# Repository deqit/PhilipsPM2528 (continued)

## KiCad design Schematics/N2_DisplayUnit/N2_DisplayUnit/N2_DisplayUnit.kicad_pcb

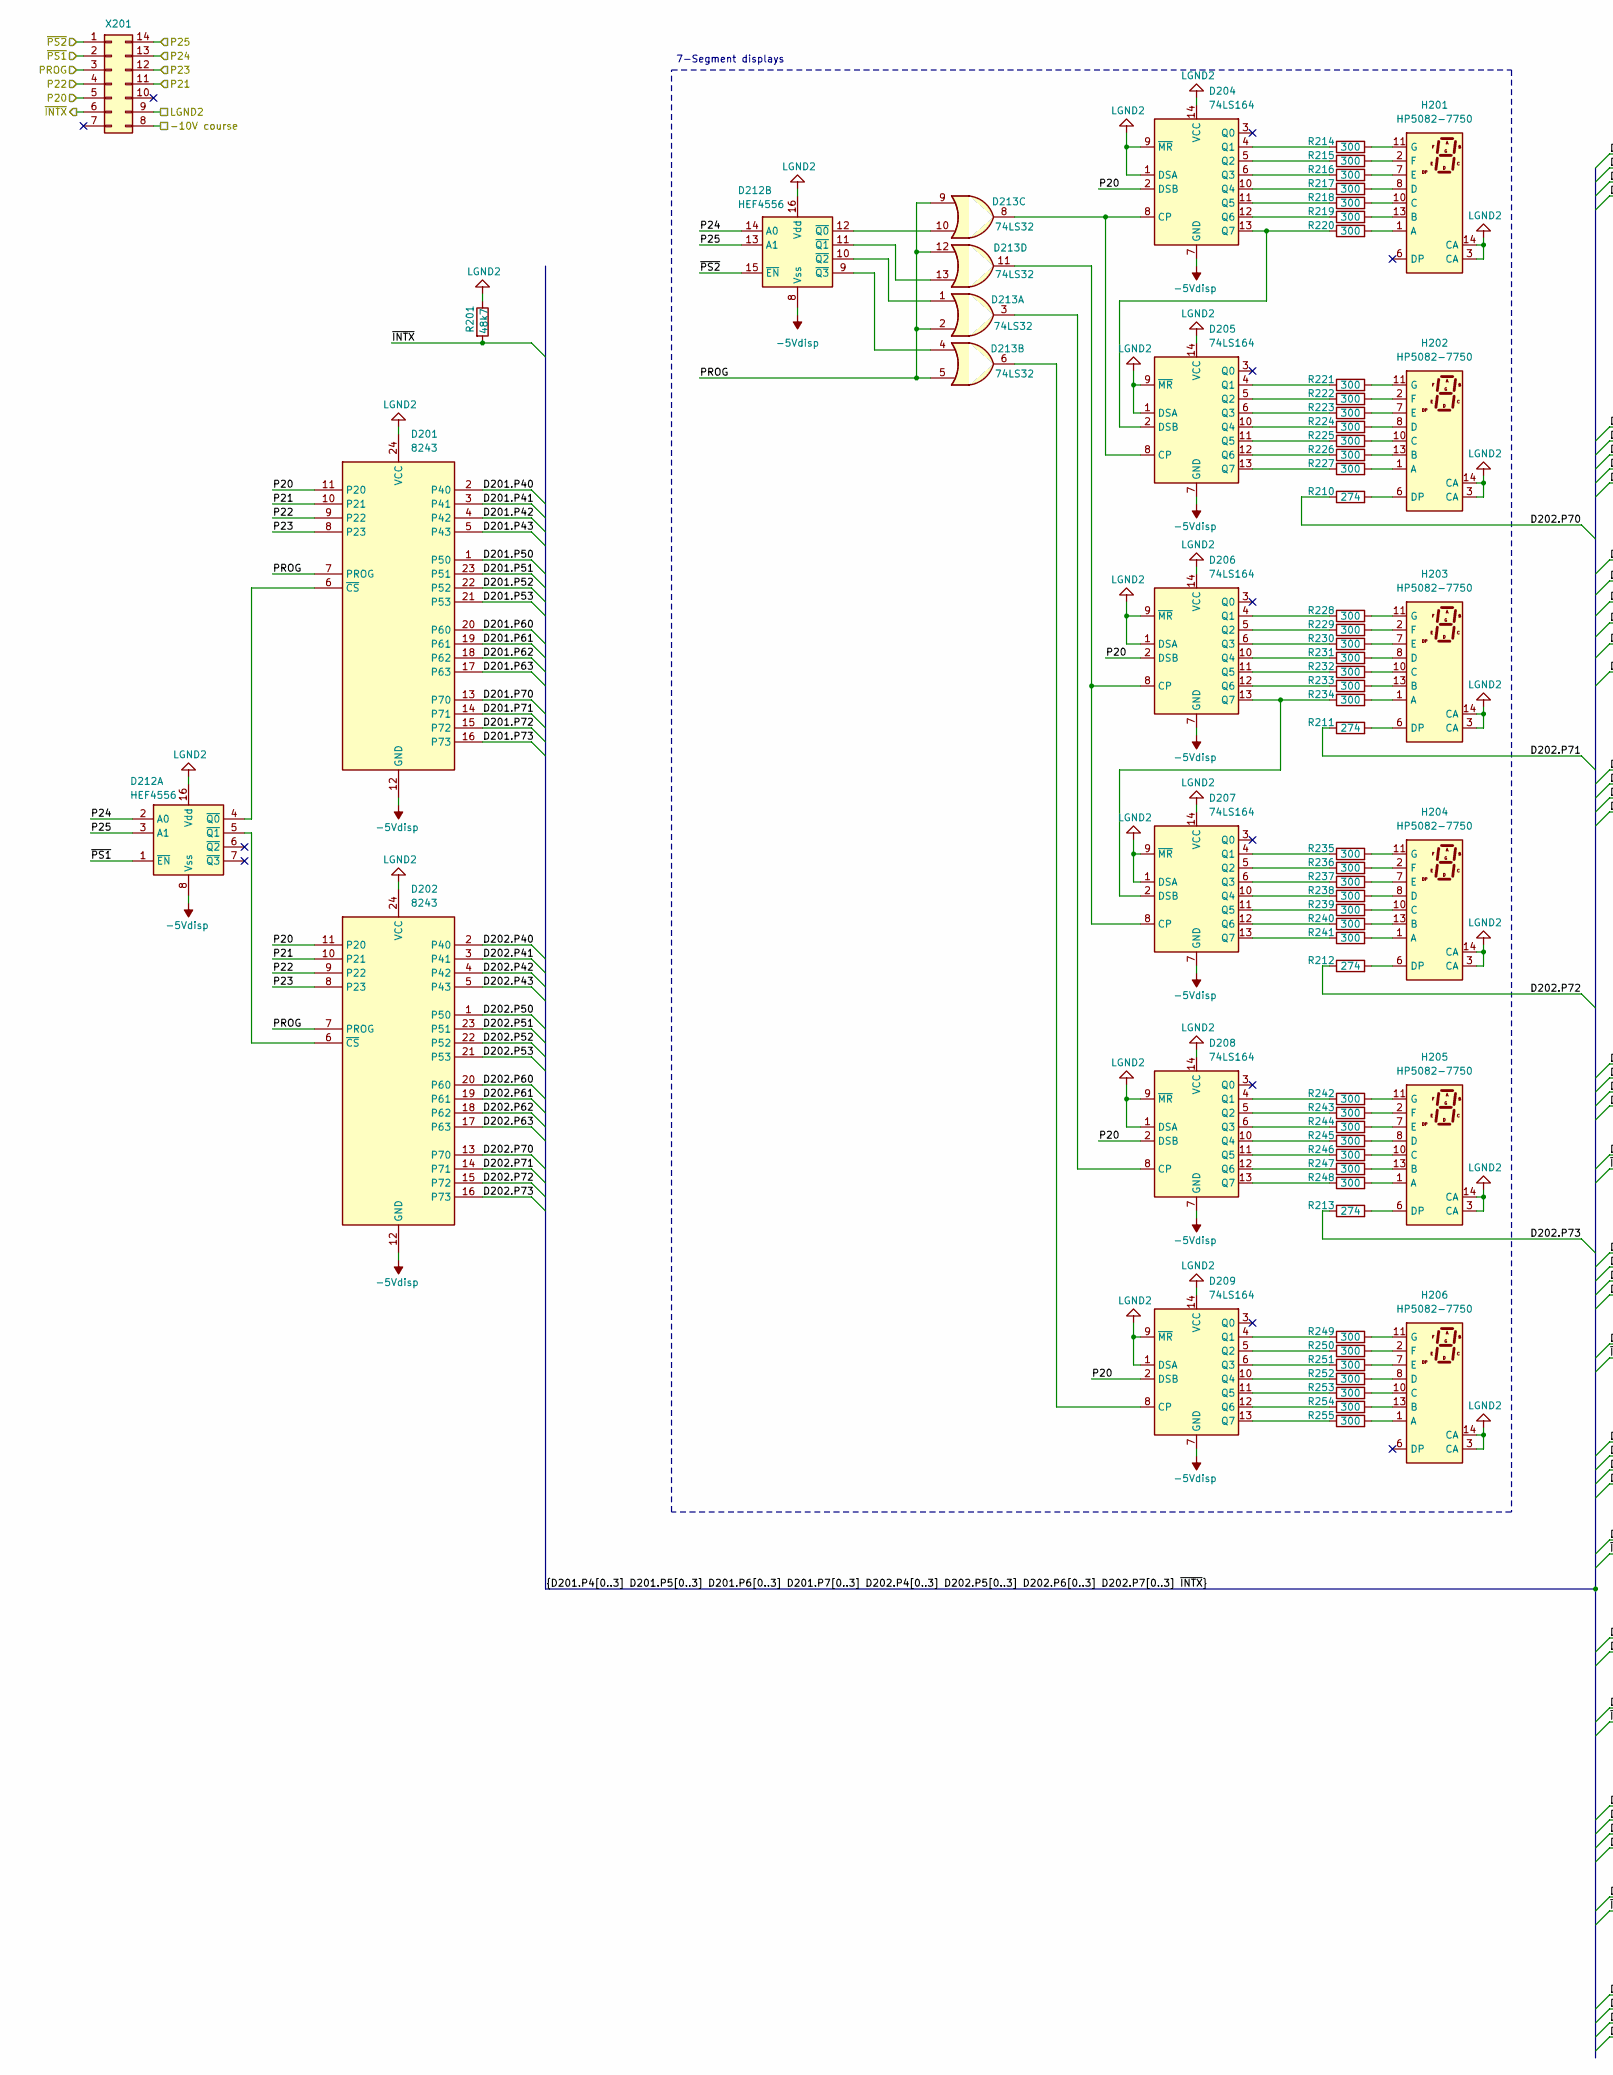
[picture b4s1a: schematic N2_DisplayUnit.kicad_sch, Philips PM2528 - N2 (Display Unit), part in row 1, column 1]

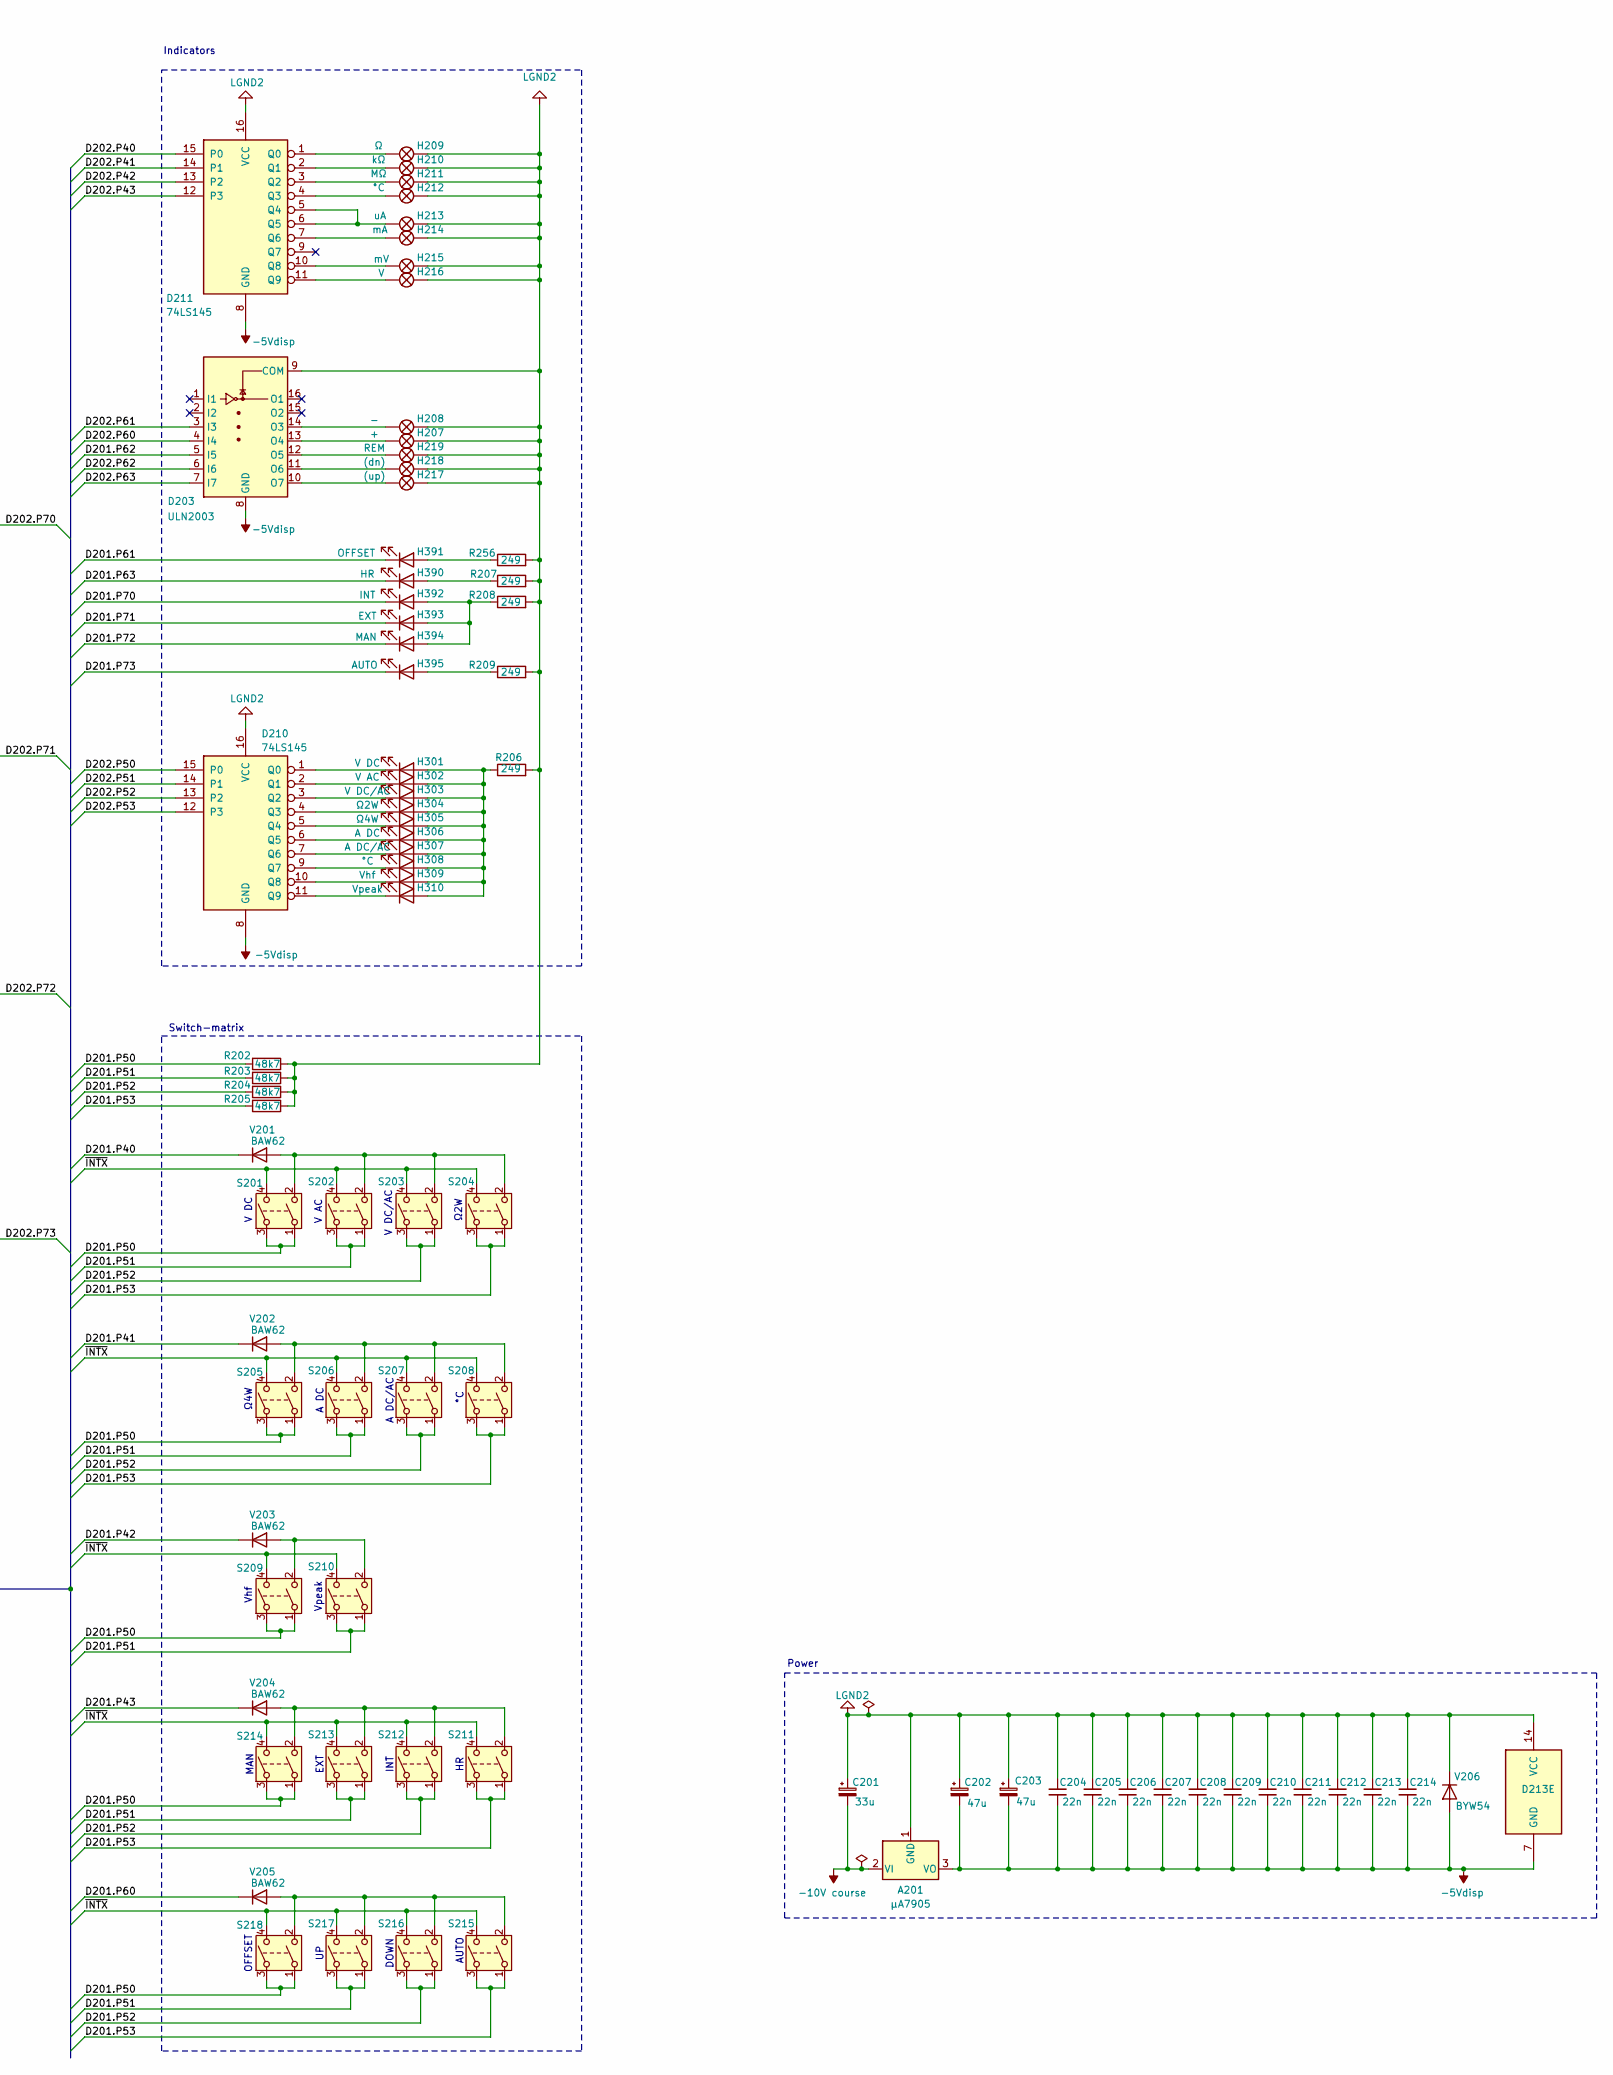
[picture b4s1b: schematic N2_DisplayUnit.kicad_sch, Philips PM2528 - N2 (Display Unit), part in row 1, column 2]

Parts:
A201: µA7905; TO-220-3_Vertical
C201: 33u; CP_Axial_L10.0mm_D4.5mm_P15.00mm_Horizontal
C202, C203: 47u; CP_Axial_L10.0mm_D4.5mm_P15.00mm_Horizontal
C204, C205, C206, C207, C208, C209, C210, C211, C212, C213, C214: 22n; C_Disc_D5.0mm_W2.5mm_P5.00mm
D201, D202: 8243; DIP-24_W15.24mm
D203: ULN2003; DIP-16_W7.62mm
D204, D205, D206, D207, D208, D209: 74LS164; DIP-14_W7.62mm
D210, D211: 74LS145; DIP-16_W7.62mm
D212: HEF4556; DIP-16_W7.62mm
D213: 74LS32; DIP-14_W7.62mm
H201, H202, H203, H204, H205, H206: HP5082-7750; MAN3820A
H207: +; LED_D3.0mm
H208: -; LED_D3.0mm
H209: Ω; LED_D3.0mm
H210: kΩ; LED_D3.0mm
H211: MΩ; LED_D3.0mm
H212, H308: °C; LED_D3.0mm
H213: uA; LED_D3.0mm
H214: mA; LED_D3.0mm
H215: mV; LED_D3.0mm
H216: V; LED_D3.0mm
H217: (up); LED_D3.0mm
H218: (dn); LED_D3.0mm
H219: REM; LED_D3.0mm
H301: V DC; LED_D3.0mm
H302: V AC; LED_D3.0mm
H303: V DC/AC; LED_D3.0mm
H304: Ω2W; LED_D3.0mm
H305: Ω4W; LED_D3.0mm
H306: A DC; LED_D3.0mm
H307: A DC/AC; LED_D3.0mm
H309: Vhf; LED_D3.0mm
H310: Vpeak; LED_D3.0mm
H390: HR; LED_D3.0mm
H391: OFFSET; LED_D3.0mm
H392: INT; LED_D3.0mm
H393: EXT; LED_D3.0mm
H394: MAN; LED_D3.0mm
H395: AUTO; LED_D3.0mm
R201, R202, R203, R204, R205: 48k7; R_Axial_DIN0207_L6.3mm_D2.5mm_P10.16mm_Horizontal
R206, R207, R208, R209, R256: 249; R_Axial_DIN0207_L6.3mm_D2.5mm_P10.16mm_Horizontal
R210, R211, R212, R213: 274; R_Axial_DIN0207_L6.3mm_D2.5mm_P10.16mm_Horizontal
R214, R215, R216, R217, R218, R219, R220, R221, R222, R223, R224, R225, R226, R227, R228, R229, R230, R231, R232, R233, R234, R235, R236, R237, R238, R239, R240, R241, R242, R243, R244, R245, R246, R247, R248, R249, R250, R251, R252, R253, R254, R255: 300; R_Axial_DIN0207_L6.3mm_D2.5mm_P2.54mm_Vertical
S201, S202, S203, S204, S205, S206, S207, S208, S209, S210, S211, S212, S213, S214, S215, S216, S217, S218: SW_DPST; SW_Push_2P1T_Toggle_CK_PVA1xxH1xxxxxxV2
V201, V202, V203, V204, V205: BAW62; D_DO-35_SOD27_P10.16mm_Horizontal
V206: BYW54; D_DO-35_SOD27_P10.16mm_Horizontal
X201: Conn_02x07_Counter_Clockwise; DIP-14_W10.16mm

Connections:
-5Vdisp: A201.3 (VO), C202.2, C203.2, C204.2, C205.2, C206.2, C207.2, C208.2, C209.2, C210.2, C211.2, C212.2, C213.2, C214.2, D201.12 (GND), D202.12 (GND), D203.8 (GND), D204.7 (GND), D205.7 (GND), D206.7 (GND), D207.7 (GND), D208.7 (GND), D209.7 (GND), D210.8 (GND), D211.8 (GND), D212.8 (Vss), D213.7 (GND), V206.2 (A)
-10V course: A201.2 (VI), C201.2, X201.8
/D201.P40: D201.2 (P40), V201.1 (K)
/D201.P41: D201.3 (P41), V202.1 (K)
/D201.P42: D201.4 (P42), V203.1 (K)
/D201.P43: D201.5 (P43), V204.1 (K)
/D201.P50: D201.1 (P50), R202.2, S201.1, S201.3, S205.1, S205.3, S209.1, S209.3, S214.1, S214.3, S218.1, S218.3
/D201.P51: D201.23 (P51), R203.2, S202.1, S202.3, S206.1, S206.3, S210.1, S210.3, S213.1, S213.3, S217.1, S217.3
/D201.P52: D201.22 (P52), R204.2, S203.1, S203.3, S207.1, S207.3, S212.1, S212.3, S216.1, S216.3
/D201.P53: D201.21 (P53), R205.2, S204.1, S204.3, S208.1, S208.3, S211.1, S211.3, S215.1, S215.3
/D201.P60: D201.20 (P60), V205.1 (K)
/D201.P61: D201.19 (P61), H391.1 (K)
/D201.P62: D201.18 (P62), D203.5 (I5)
/D201.P63: D201.17 (P63), H390.1 (K)
/D201.P70: D201.13 (P70), H392.1 (K)
/D201.P71: D201.14 (P71), H393.1 (K)
/D201.P72: D201.15 (P72), H394.1 (K)
/D201.P73: D201.16 (P73), H395.1 (K)
/D202.P40: D202.2 (P40), D211.15 (P0)
/D202.P41: D202.3 (P41), D211.14 (P1)
/D202.P42: D202.4 (P42), D211.13 (P2)
/D202.P43: D202.5 (P43), D211.12 (P3)
/D202.P50: D202.1 (P50), D210.15 (P0)
/D202.P51: D202.23 (P51), D210.14 (P1)
/D202.P52: D202.22 (P52), D210.13 (P2)
/D202.P53: D202.21 (P53), D210.12 (P3)
/D202.P60: D202.20 (P60), D203.4 (I4)
/D202.P61: D202.19 (P61), D203.3 (I3)
/D202.P62: D202.18 (P62), D203.6 (I6)
/D202.P63: D202.17 (P63), D203.7 (I7)
/D202.P70: D202.13 (P70), R210.1
/D202.P71: D202.14 (P71), R211.1
/D202.P72: D202.15 (P72), R212.1
/D202.P73: D202.16 (P73), R213.1
/LGND2: A201.1 (GND), C201.1, C202.1, C203.1, C204.1, C205.1, C206.1, C207.1, C208.1, C209.1, C210.1, C211.1, C212.1, C213.1, C214.1, D201.24 (VCC), D202.24 (VCC), D203.9 (COM), D204.1 (DSA), D204.9 (~MR), D204.14 (VCC), D205.1 (DSA), D205.9 (~MR), D205.14 (VCC), D206.1 (DSA), D206.9 (~MR), D206.14 (VCC), D207.1 (DSA), D207.9 (~MR), D207.14 (VCC), D208.1 (DSA), D208.9 (~MR), D208.14 (VCC), D209.1 (DSA), D209.9 (~MR), D209.14 (VCC), D210.16 (VCC), D211.16 (VCC), D212.16 (Vdd), D213.14 (VCC), H201.3 (CA), H201.14 (CA), H202.3 (CA), H202.14 (CA), H203.3 (CA), H203.14 (CA), H204.3 (CA), H204.14 (CA), H205.3 (CA), H205.14 (CA), H206.3 (CA), H206.14 (CA), H207.2, H208.2, H209.2, H210.2, H211.2, H212.2, H213.2, H214.2, H215.2, H216.2, H217.2, H218.2, H219.2, R201.1, R202.1, R203.1, R204.1, R205.1, R206.2, R207.2, R208.2, R209.2, R256.2, V206.1 (K), X201.9
/P20: D201.11 (P20), D202.11 (P20), D204.2 (DSB), D206.2 (DSB), D208.2 (DSB), D209.2 (DSB), X201.5
/P21: D201.10 (P21), D202.10 (P21), X201.11
/P22: D201.9 (P22), D202.9 (P22), X201.4
/P23: D201.8 (P23), D202.8 (P23), X201.12
/P24: D212.2 (A0), D212.14 (A0), X201.13
/P25: D212.3 (A1), D212.13 (A1), X201.14
/PROG: D201.7 (PROG), D202.7 (PROG), D213.2, D213.5, D213.9, D213.12, X201.3
/~INTX: R201.2, S201.4, S202.4, S203.4, S204.4, S205.4, S206.4, S207.4, S208.4, S209.4, S210.4, S211.4, S212.4, S213.4, S214.4, S215.4, S216.4, S217.4, S218.4, X201.6
/~PS1: D212.1 (~EN), X201.2
/~PS2: D212.15 (~EN), X201.1
unnamed: D201.6 (~CS), D212.4 (~Q0)
unnamed: D202.6 (~CS), D212.5 (~Q1)
unnamed: D203.14 (O3), H208.1
unnamed: D203.13 (O4), H207.1
unnamed: D203.12 (O5), H219.1
unnamed: D203.11 (O6), H218.1
unnamed: D203.10 (O7), H217.1
unnamed: D204.8 (CP), D205.8 (CP), D213.8
unnamed: D204.4 (Q1), R214.1
unnamed: D204.5 (Q2), R215.1
unnamed: D204.6 (Q3), R216.1
unnamed: D204.10 (Q4), R217.1
unnamed: D204.11 (Q5), R218.1
unnamed: D204.12 (Q6), R219.1
unnamed: D204.13 (Q7), D205.2 (DSB), R220.1
unnamed: D205.4 (Q1), R221.1
unnamed: D205.5 (Q2), R222.1
unnamed: D205.6 (Q3), R223.1
unnamed: D205.10 (Q4), R224.1
unnamed: D205.11 (Q5), R225.1
unnamed: D205.12 (Q6), R226.1
unnamed: D205.13 (Q7), R227.1
unnamed: D206.8 (CP), D207.8 (CP), D213.11
unnamed: D206.4 (Q1), R228.1
unnamed: D206.5 (Q2), R229.1
unnamed: D206.6 (Q3), R230.1
unnamed: D206.10 (Q4), R231.1
unnamed: D206.11 (Q5), R232.1
unnamed: D206.12 (Q6), R233.1
unnamed: D206.13 (Q7), D207.2 (DSB), R234.1
unnamed: D207.4 (Q1), R235.1
unnamed: D207.5 (Q2), R236.1
unnamed: D207.6 (Q3), R237.1
unnamed: D207.10 (Q4), R238.1
unnamed: D207.11 (Q5), R239.1
unnamed: D207.12 (Q6), R240.1
unnamed: D207.13 (Q7), R241.1
unnamed: D208.8 (CP), D213.3
unnamed: D208.4 (Q1), R242.1
unnamed: D208.5 (Q2), R243.1
unnamed: D208.6 (Q3), R244.1
unnamed: D208.10 (Q4), R245.1
unnamed: D208.11 (Q5), R246.1
unnamed: D208.12 (Q6), R247.1
unnamed: D208.13 (Q7), R248.1
unnamed: D209.8 (CP), D213.6
unnamed: D209.4 (Q1), R249.1
unnamed: D209.5 (Q2), R250.1
unnamed: D209.6 (Q3), R251.1
unnamed: D209.10 (Q4), R252.1
unnamed: D209.11 (Q5), R253.1
unnamed: D209.12 (Q6), R254.1
unnamed: D209.13 (Q7), R255.1
unnamed: D210.1 (Q0), H301.1 (K)
unnamed: D210.2 (Q1), H302.1 (K)
unnamed: D210.3 (Q2), H303.1 (K)
unnamed: D210.4 (Q3), H304.1 (K)
unnamed: D210.5 (Q4), H305.1 (K)
unnamed: D210.6 (Q5), H306.1 (K)
unnamed: D210.7 (Q6), H307.1 (K)
unnamed: D210.9 (Q7), H308.1 (K)
unnamed: D210.10 (Q8), H309.1 (K)
unnamed: D210.11 (Q9), H310.1 (K)
unnamed: D211.1 (Q0), H209.1
unnamed: D211.2 (Q1), H210.1
unnamed: D211.3 (Q2), H211.1
unnamed: D211.4 (Q3), H212.1
unnamed: D211.5 (Q4), D211.6 (Q5), H213.1
unnamed: D211.7 (Q6), H214.1
unnamed: D211.10 (Q8), H215.1
unnamed: D211.11 (Q9), H216.1
unnamed: D212.12 (~Q0), D213.10
unnamed: D212.11 (~Q1), D213.13
unnamed: D212.10 (~Q2), D213.1
unnamed: D212.9 (~Q3), D213.4
unnamed: H201.1 (A), R220.2
unnamed: H201.13 (B), R219.2
unnamed: H201.10 (C), R218.2
unnamed: H201.8 (D), R217.2
unnamed: H201.7 (E), R216.2
unnamed: H201.2 (F), R215.2
unnamed: H201.11 (G), R214.2
unnamed: H202.1 (A), R227.2
unnamed: H202.13 (B), R226.2
unnamed: H202.10 (C), R225.2
unnamed: H202.8 (D), R224.2
unnamed: H202.6 (DP), R210.2
unnamed: H202.7 (E), R223.2
unnamed: H202.2 (F), R222.2
unnamed: H202.11 (G), R221.2
unnamed: H203.1 (A), R234.2
unnamed: H203.13 (B), R233.2
unnamed: H203.10 (C), R232.2
unnamed: H203.8 (D), R231.2
unnamed: H203.6 (DP), R211.2
unnamed: H203.7 (E), R230.2
unnamed: H203.2 (F), R229.2
unnamed: H203.11 (G), R228.2
unnamed: H204.1 (A), R241.2
unnamed: H204.13 (B), R240.2
unnamed: H204.10 (C), R239.2
unnamed: H204.8 (D), R238.2
unnamed: H204.6 (DP), R212.2
unnamed: H204.7 (E), R237.2
unnamed: H204.2 (F), R236.2
unnamed: H204.11 (G), R235.2
unnamed: H205.1 (A), R248.2
unnamed: H205.13 (B), R247.2
unnamed: H205.10 (C), R246.2
unnamed: H205.8 (D), R245.2
unnamed: H205.6 (DP), R213.2
unnamed: H205.7 (E), R244.2
unnamed: H205.2 (F), R243.2
unnamed: H205.11 (G), R242.2
unnamed: H206.1 (A), R255.2
unnamed: H206.13 (B), R254.2
unnamed: H206.10 (C), R253.2
unnamed: H206.8 (D), R252.2
unnamed: H206.7 (E), R251.2
unnamed: H206.2 (F), R250.2
unnamed: H206.11 (G), R249.2
unnamed: H301.2 (A), H302.2 (A), H303.2 (A), H304.2 (A), H305.2 (A), H306.2 (A), H307.2 (A), H308.2 (A), H309.2 (A), H310.2 (A), R206.1
unnamed: H390.2 (A), R207.1
unnamed: H391.2 (A), R256.1
unnamed: H392.2 (A), H393.2 (A), H394.2 (A), R208.1
unnamed: H395.2 (A), R209.1
unnamed: S201.2, S202.2, S203.2, S204.2, V201.2 (A)
unnamed: S205.2, S206.2, S207.2, S208.2, V202.2 (A)
unnamed: S209.2, S210.2, V203.2 (A)
unnamed: S211.2, S212.2, S213.2, S214.2, V204.2 (A)
unnamed: S215.2, S216.2, S217.2, S218.2, V205.2 (A)

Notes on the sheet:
Vhf
AUTO
Power
OFFSET
MAN
DOWN
V AC
Indicators
V DC
Switch-matrix
A DC
V DC/AC
Vpeak
EXT
7-Segment displays
Ω4W
Ω2W
A DC/AC
INT

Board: 2 copper layers, 144 parts (0 on the bottom side), 176 nets, no tracks yet.

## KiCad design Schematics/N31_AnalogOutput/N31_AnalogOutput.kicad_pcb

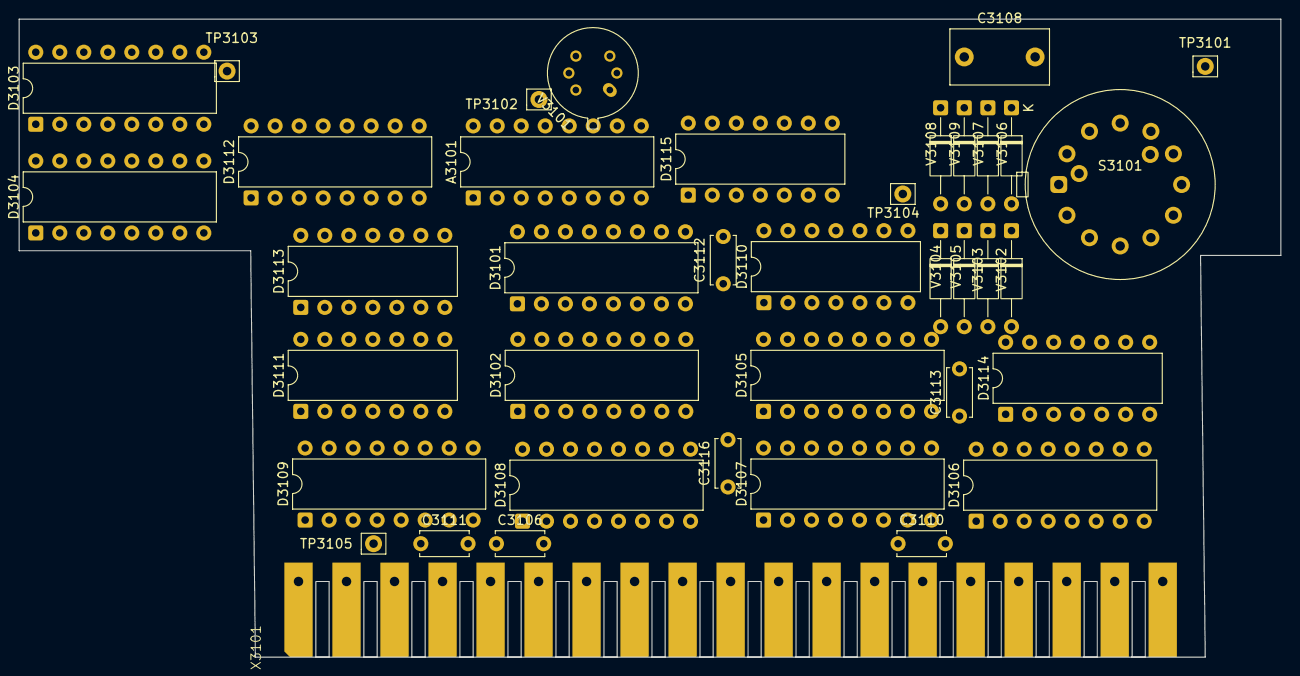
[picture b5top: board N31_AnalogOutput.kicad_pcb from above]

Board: 2 copper layers, 133.5 x 67.5 mm, 39 parts (0 on the bottom side), 71 nets, no tracks yet.

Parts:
A3101: OQ0051; DIP-16_W7.62mm
C3106, C3110, C3111, C3112, C3113, C3116: 22n; C_Disc_D5.0mm_W2.5mm_P5.00mm
C3108: 22n; C_Rect_L10.3mm_W5.7mm_P7.50mm_MKS4
D3101, D3102: HEF4094B; DIP-16_W7.62mm
D3103, D3104: HEF4040B; DIP-16_W7.62mm
D3105: HEF4008B; DIP-16_W7.62mm
D3106, D3107, D3108, D3109: HEF4522B; DIP-16_W7.62mm
D3110: HEF4085B; DIP-14_W7.62mm
D3111: HEF4011B; DIP-14_W7.62mm
D3112: HEF4049B; DIP-16_W7.62mm
D3113: HEF4073B; DIP-14_W7.62mm
D3114: HEF4081B; DIP-14_W7.62mm
D3115: HEF4066B; DIP-14_W7.62mm
S3101: DIGIT SELECT; RotarySwitch_1x7_S3101
TP3101: 0V; Pin_D0.9mm_L10.0mm_W2.4mm_FlatFork
TP3102: OUT; Pin_D0.9mm_L10.0mm_W2.4mm_FlatFork
TP3103: ≈850kHz; Pin_D0.9mm_L10.0mm_W2.4mm_FlatFork
TP3104: -7V; Pin_D0.9mm_L10.0mm_W2.4mm_FlatFork
TP3105: TerminalCount; Pin_D0.9mm_L10.0mm_W2.4mm_FlatFork
V3101: BFQ12; TO-75-6
V3102, V3103, V3104, V3105, V3106, V3107, V3108, V3109: BAW62; D_DO-35_SOD27_P10.16mm_Horizontal
X3101: PM2528Edgeconnector

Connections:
+5VOG: A3101.12 (V+), C3110.1, C3111.1, C3112.1, C3113.1, D3101.15 (EO), D3101.16 (VDD), D3102.15 (EO), D3102.16 (VDD), D3103.16 (VDD), D3104.16 (VDD), D3105.16 (VDD), D3106.13 (CF), D3106.16 (VDD), D3107.16 (VDD), D3108.16 (VDD), D3109.16 (VDD), D3110.14 (VDD), D3111.14 (VDD), D3112.1 (VDD), D3113.14 (VDD), D3114.14 (VDD), D3115.14 (VDD), S3101.8, X3101.5
-7V: A3101.1 (V-), C3116.2, TP3104.1 (1_1)
/CLOCK: D3113.13 (I9), X3101.19
/DATA: D3101.2 (D), X3101.18
/DLEN1: D3112.14 (6A), D3113.12 (I8), X3101.17
/HI: C3106.2, X3101.15
/LOAD: D3104.11 (MR), D3106.3 (PL), D3107.3 (PL), D3108.3 (PL), D3109.3 (PL), D3111.3 (O1)
/O0: D3102.4 (O0), D3108.2 (P3)
/O1: D3102.5 (O1), D3108.14 (P2)
/O2: D3102.6 (O2), D3108.11 (P1)
/O3: D3102.7 (O3), D3108.5 (P0)
/O4: D3102.14 (O4), D3109.2 (P3)
/O5: D3102.13 (O5), D3109.14 (P2)
/O6: D3102.12 (O6), D3109.11 (P1)
/O7: D3102.11 (O7), D3109.5 (P0)
/OP2: D3101.6 (O2), D3114.8 (I5)
/OP3: D3101.7 (O3), D3114.5 (I3)
/OP4: D3101.14 (O4), D3105.1 (A3), D3110.11 (B4)
/OP5: D3101.13 (O5), D3105.3 (A2), D3110.6 (B1), D3110.8 (B2)
/OP6: D3101.12 (O6), D3105.5 (A1), D3110.5 (B0)
/OP7: D3101.11 (O7), D3105.7 (A0), D3110.9 (B3)
/xDIGITSELECT_A: D3111.8 (I5), D3111.9 (I6), D3113.5 (I3), D3114.6 (I4), D3114.9 (I6), S3101.1
/xDIGITSELECT_C: D3105.6 (B0), D3114.1 (I1), D3114.13 (I8), S3101.3, V3103.1, V3105.1
/xDIGITSELECT_D: D3110.12 (A2), S3101.4, V3102.1
/xDIGITSELECT_F: D3110.2 (A1), S3101.6, V3104.1
/xOSC: D3104.10 (~CP), D3109.6 (CP0), D3112.4 (2Y), D3112.9 (4A), D3112.11 (5A), TP3103.1 (1_1)
/~Os: D3101.10 (O'_{S}), D3102.2 (D)
GNDOG: C3106.1, C3108.2, C3110.2, C3111.2, C3112.2, C3113.2, C3116.1, D3101.8 (VSS), D3102.8 (VSS), D3103.8 (VSS), D3104.8 (VSS), D3105.8 (VSS), D3105.9 (C_{IN}), D3106.2 (P3), D3106.4 (~CP1), D3106.8 (VSS), D3106.10 (MR), D3106.14 (P2), D3107.4 (~CP1), D3107.8 (VSS), D3107.10 (MR), D3108.4 (~CP1), D3108.8 (VSS), D3108.10 (MR), D3109.8 (VSS), D3109.10 (MR), D3110.7 (VSS), D3110.10 (A4), D3111.7 (VSS), D3112.8 (VSS), D3113.7 (VSS), D3114.7 (VSS), D3115.1 (Y0), D3115.3 (Z1), D3115.7 (VSS), D3115.9 (Z2), D3115.13 (E0), TP3101.1 (1_1), V3106.1, X3101.1, X3101.14
unnamed: A3101.15 (D_{IN+}), V3101.2 (D)
unnamed: A3101.14 (D_{IN-}), V3101.5 (D)
unnamed: A3101.4 (OUT2), A3101.5, TP3102.1 (1_1), V3101.6 (G)
unnamed: C3108.1, V3101.3 (G)
unnamed: D3101.3 (CP), D3102.3 (CP), D3103.10 (~CP), D3113.10 (O3)
unnamed: D3101.1 (STR), D3102.1 (STR), D3103.11 (MR), D3112.15 (6Y)
unnamed: D3103.6 (O2), D3113.2 (I5), D3113.8 (I6)
unnamed: D3103.3 (O4), D3110.1 (A0), D3113.1 (I4)
unnamed: D3104.14 (O9), D3113.4 (I2)
unnamed: D3104.15 (O10), D3111.6 (I4)
unnamed: D3104.1 (O11), D3113.3 (I1)
unnamed: D3105.4 (B1), D3105.15 (B3), D3114.11 (O4)
unnamed: D3105.2 (B2), D3114.3 (O1)
unnamed: D3105.10 (S0), D3107.5 (P0)
unnamed: D3105.11 (S1), D3107.11 (P1)
unnamed: D3105.12 (S2), D3107.14 (P2)
unnamed: D3105.13 (S3), D3107.2 (P3)
unnamed: D3106.6 (CP0), D3107.1 (O3)
unnamed: D3106.5 (P0), D3114.4 (O2)
unnamed: D3106.11 (P1), D3114.10 (O3)
unnamed: D3106.12 (TC), D3107.13 (CF)
unnamed: D3107.6 (CP0), D3108.1 (O3)
unnamed: D3107.12 (TC), D3108.13 (CF)
unnamed: D3108.6 (CP0), D3109.1 (O3)
unnamed: D3108.12 (TC), D3109.13 (CF)
unnamed: D3109.4 (~CP1), D3109.12 (TC), D3115.5 (E1), D3115.6 (E2), TP3105.1 (1_1)
unnamed: D3110.13 (A3), D3113.9 (O2)
unnamed: D3110.3 (OA), D3113.11 (I7)
unnamed: D3110.4 (OB), D3112.3 (1A), D3114.2 (I2)
unnamed: D3111.1 (I1), D3111.11 (O4)
unnamed: D3111.2 (I2), D3111.4 (O2)
unnamed: D3111.5 (I3), D3111.10 (O3)
unnamed: D3111.12 (I7), D3111.13 (I8), D3113.6 (O1)
unnamed: D3112.2 (1Y), D3114.12 (I7)
unnamed: D3112.5 (2A), D3112.6 (3Y)
unnamed: D3112.10 (4Y), D3112.12 (5Y)
unnamed: D3115.4 (Y1), D3115.12 (E3)
unnamed: D3115.8 (Y2), D3115.10 (Z3)
unnamed: S3101.5, V3102.2, V3103.2
unnamed: S3101.7, V3104.2, V3105.2
unnamed: V3106.2, V3107.1
unnamed: V3107.2, V3108.1
unnamed: V3108.2, V3109.1

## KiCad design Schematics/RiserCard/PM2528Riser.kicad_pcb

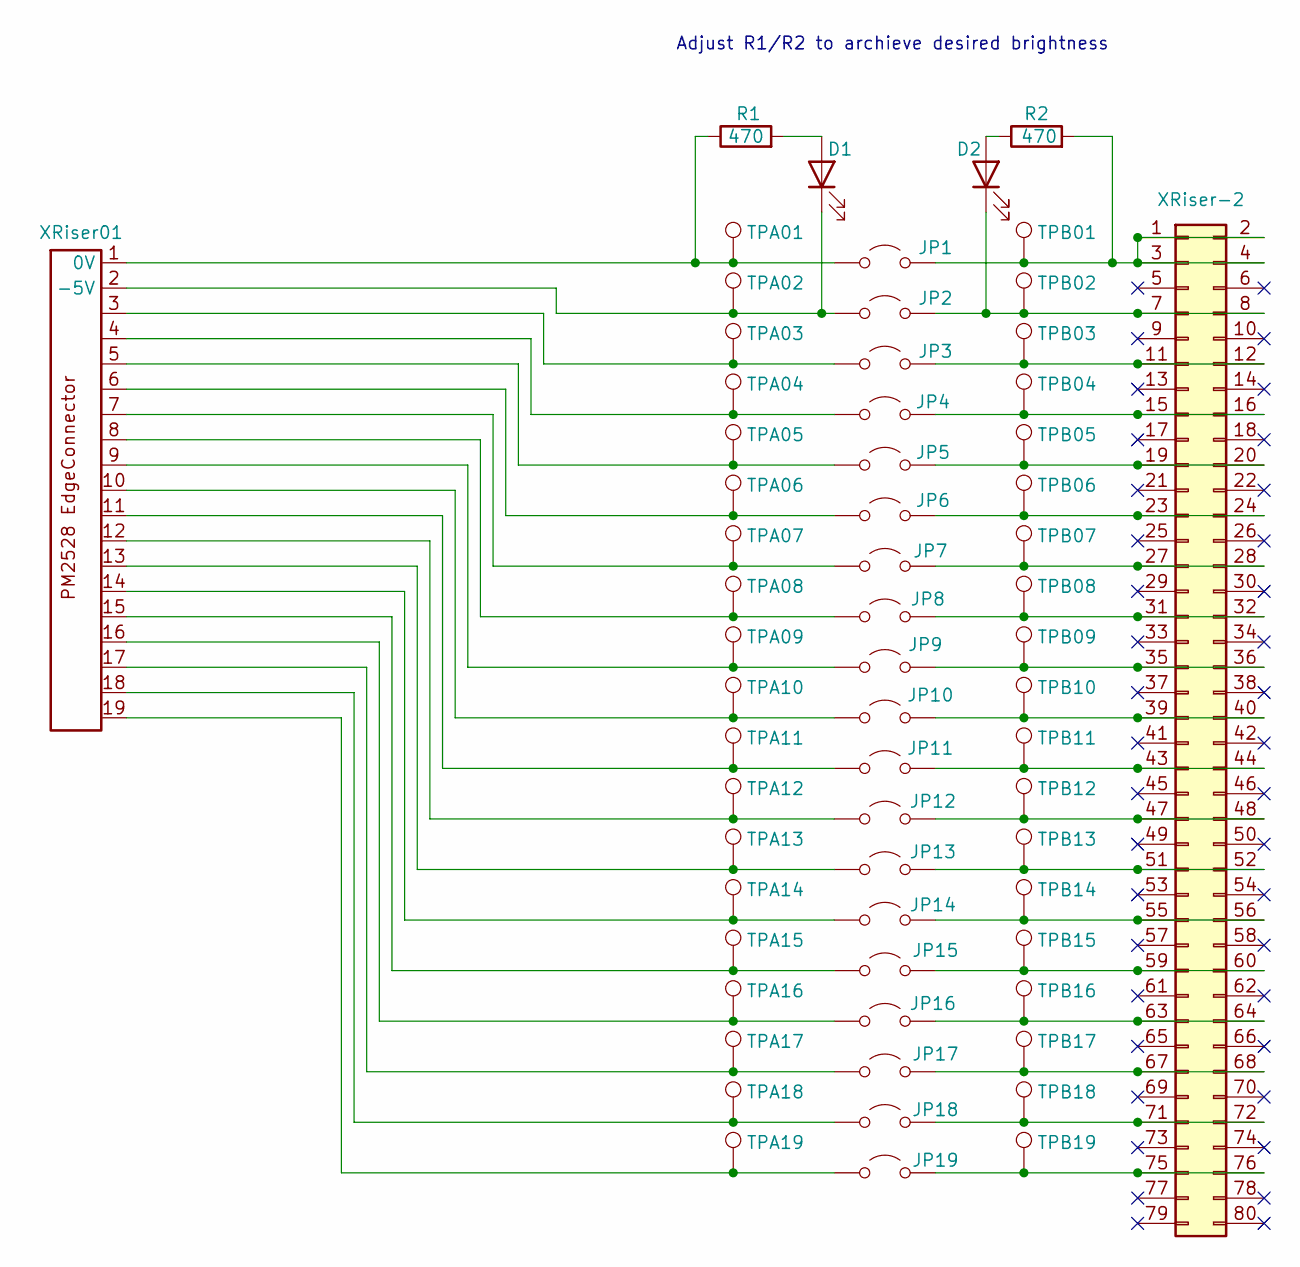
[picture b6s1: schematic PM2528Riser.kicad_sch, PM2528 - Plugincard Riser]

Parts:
D1, D2: LED; LED_0805_2012Metric
JP1, JP2, JP3, JP4, JP5, JP6, JP7, JP8, JP9, JP10, JP11, JP12, JP13, JP14, JP15, JP16, JP17, JP18, JP19: Jumper_2_Open; PinHeader_1x02_P2.54mm_Vertical
R1, R2: 470; R_0805_2012Metric_Pad1.20x1.40mm_HandSolder
TPA01, TPA02, TPA03, TPA04, TPA05, TPA06, TPA07, TPA08, TPA09, TPA10, TPA11, TPA12, TPA13, TPA14, TPA15, TPA16, TPA17, TPA18, TPA19: TestPoint; Pin_D1.0mm_L10.0mm
TPB01, TPB02, TPB03, TPB04, TPB05, TPB06, TPB07, TPB08, TPB09, TPB10, TPB11, TPB12, TPB13, TPB14, TPB15, TPB16, TPB17, TPB18, TPB19: TestPoint; TestPoint_Loop_D1.80mm_Drill1.0mm_Beaded
XRiser01: PM2528_RiserCardConnector
XRiser-2: Conn_02x40_Odd_Even; CONN EDGE DUAL FMALE 80POS 0.100

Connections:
unnamed: D1.2 (A), R1.2
unnamed: D1.1 (K), JP2.1 (A), TPA02.1, XRiser01.2 (-5V)
unnamed: D2.2 (A), R2.1
unnamed: D2.1 (K), JP2.2 (B), TPB02.1, XRiser-2.7, XRiser-2.8
unnamed: JP1.1 (A), R1.1, TPA01.1, XRiser01.1 (0V)
unnamed: JP1.2 (B), R2.2, TPB01.1, XRiser-2.1, XRiser-2.2, XRiser-2.3, XRiser-2.4
unnamed: JP3.1 (A), TPA03.1, XRiser01.3
unnamed: JP3.2 (B), TPB03.1, XRiser-2.11, XRiser-2.12
unnamed: JP4.1 (A), TPA04.1, XRiser01.4
unnamed: JP4.2 (B), TPB04.1, XRiser-2.15, XRiser-2.16
unnamed: JP5.1 (A), TPA05.1, XRiser01.5
unnamed: JP5.2 (B), TPB05.1, XRiser-2.19, XRiser-2.20
unnamed: JP6.1 (A), TPA06.1, XRiser01.6
unnamed: JP6.2 (B), TPB06.1, XRiser-2.23, XRiser-2.24
unnamed: JP7.1 (A), TPA07.1, XRiser01.7
unnamed: JP7.2 (B), TPB07.1, XRiser-2.27, XRiser-2.28
unnamed: JP8.1 (A), TPA08.1, XRiser01.8
unnamed: JP8.2 (B), TPB08.1, XRiser-2.31, XRiser-2.32
unnamed: JP9.1 (A), TPA09.1, XRiser01.9
unnamed: JP9.2 (B), TPB09.1, XRiser-2.35, XRiser-2.36
unnamed: JP10.1 (A), TPA10.1, XRiser01.10
unnamed: JP10.2 (B), TPB10.1, XRiser-2.39, XRiser-2.40
unnamed: JP11.1 (A), TPA11.1, XRiser01.11
unnamed: JP11.2 (B), TPB11.1, XRiser-2.43, XRiser-2.44
unnamed: JP12.1 (A), TPA12.1, XRiser01.12
unnamed: JP12.2 (B), TPB12.1, XRiser-2.47, XRiser-2.48
unnamed: JP13.1 (A), TPA13.1, XRiser01.13
unnamed: JP13.2 (B), TPB13.1, XRiser-2.51, XRiser-2.52
unnamed: JP14.1 (A), TPA14.1, XRiser01.14
unnamed: JP14.2 (B), TPB14.1, XRiser-2.55, XRiser-2.56
unnamed: JP15.1 (A), TPA15.1, XRiser01.15
unnamed: JP15.2 (B), TPB15.1, XRiser-2.59, XRiser-2.60
unnamed: JP16.1 (A), TPA16.1, XRiser01.16
unnamed: JP16.2 (B), TPB16.1, XRiser-2.63, XRiser-2.64
unnamed: JP17.1 (A), TPA17.1, XRiser01.17
unnamed: JP17.2 (B), TPB17.1, XRiser-2.67, XRiser-2.68
unnamed: JP18.1 (A), TPA18.1, XRiser01.18
unnamed: JP18.2 (B), TPB18.1, XRiser-2.71, XRiser-2.72
unnamed: JP19.1 (A), TPA19.1, XRiser01.19
unnamed: JP19.2 (B), TPB19.1, XRiser-2.75, XRiser-2.76

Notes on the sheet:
Adjust R1/R2 to archieve desired brightness

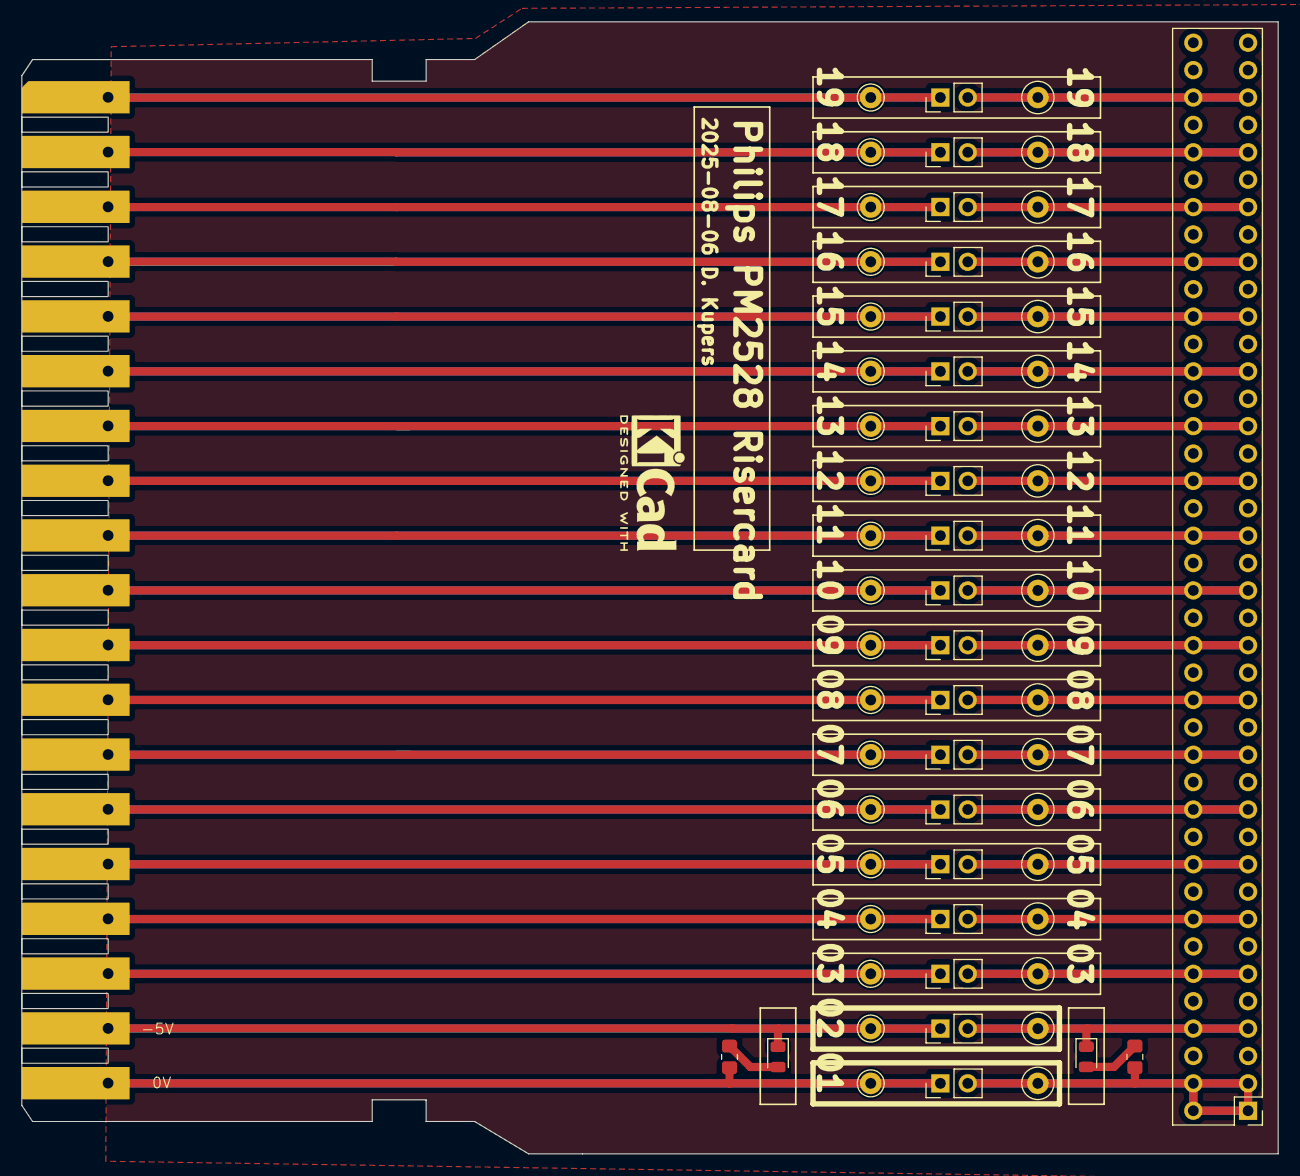
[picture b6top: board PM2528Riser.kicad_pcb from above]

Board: 2 copper layers, 116.5 x 105.0 mm, 63 parts (0 on the bottom side), 40 nets.
